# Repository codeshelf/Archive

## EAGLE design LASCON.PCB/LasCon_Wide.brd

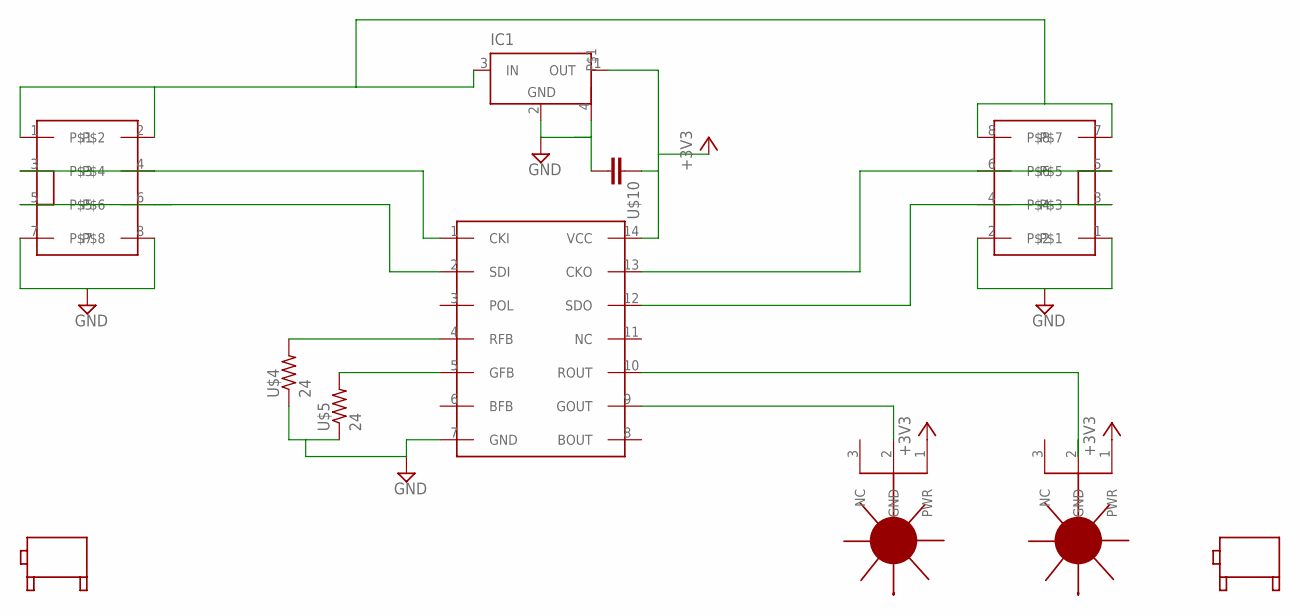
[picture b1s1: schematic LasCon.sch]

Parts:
IC1: MCP1804T-3302I; SOT223
U$1, U$2: 2X4IDC; 2X04
U$3: WS2801; SO14
U$4, U$5: 24; RF-C0805
U$6, U$7: LASER
U$8, U$9: 90DEGMNT
U$10: RF-C0805; C0805

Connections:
+3V3: IC1.1 (OUT), U$3.14 (VCC), U$6.1 (PWR), U$7.1 (PWR), U$10.1
GND: IC1.2 (GND), IC1.4, U$1.7, U$1.8, U$2.1, U$2.2, U$3.7 (GND), U$4.1, U$5.1, U$10.2
unnamed: IC1.3 (IN), U$1.1, U$1.2, U$2.7, U$2.8
unnamed: U$3.9 (GOUT), U$6.2 (GND)
unnamed: U$3.10 (ROUT), U$7.2 (GND)
unnamed: U$1.3, U$1.4, U$3.1 (CKI)
unnamed: U$1.5, U$1.6, U$3.2 (SDI)
unnamed: U$2.5, U$2.6, U$3.13 (CKO)
unnamed: U$2.3, U$2.4, U$3.12 (SDO)
unnamed: U$3.4 (RFB), U$4.2
unnamed: U$3.5 (GFB), U$5.2

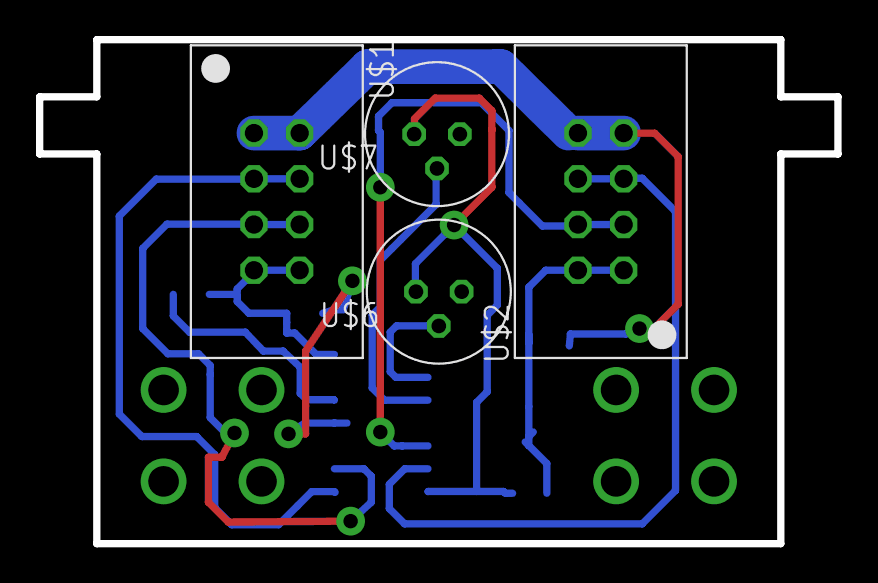
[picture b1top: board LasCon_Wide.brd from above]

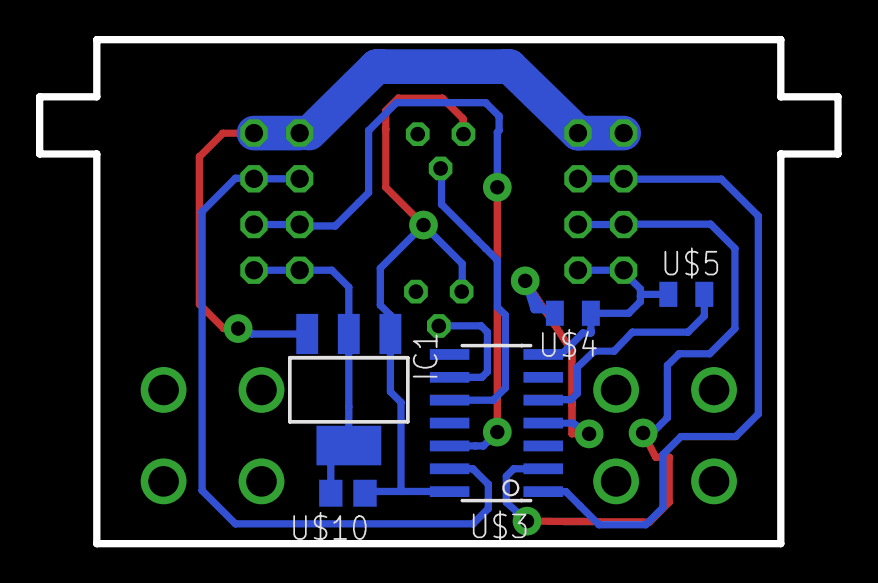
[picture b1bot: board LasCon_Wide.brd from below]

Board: 2 copper layers, 44.4 x 28.0 mm, 11 parts (5 on the bottom side), 11 nets.

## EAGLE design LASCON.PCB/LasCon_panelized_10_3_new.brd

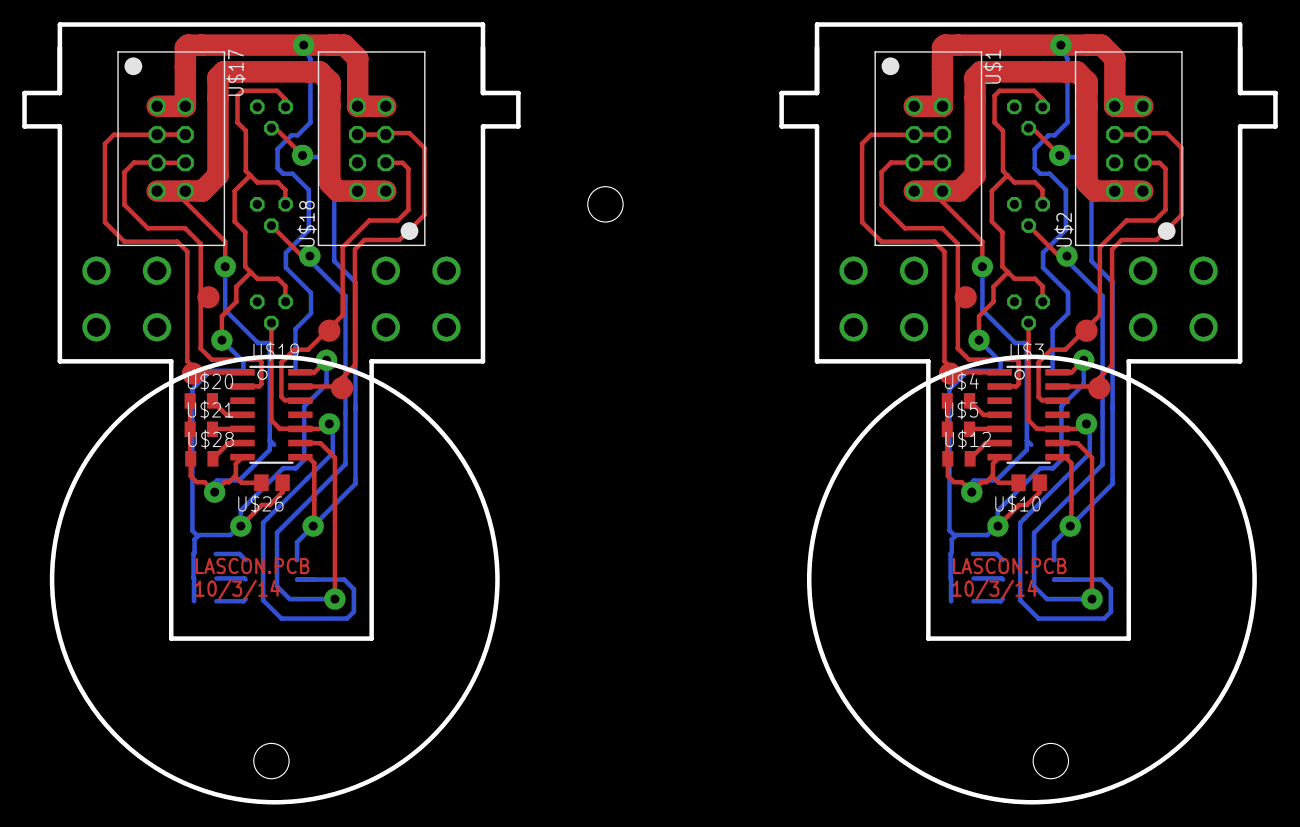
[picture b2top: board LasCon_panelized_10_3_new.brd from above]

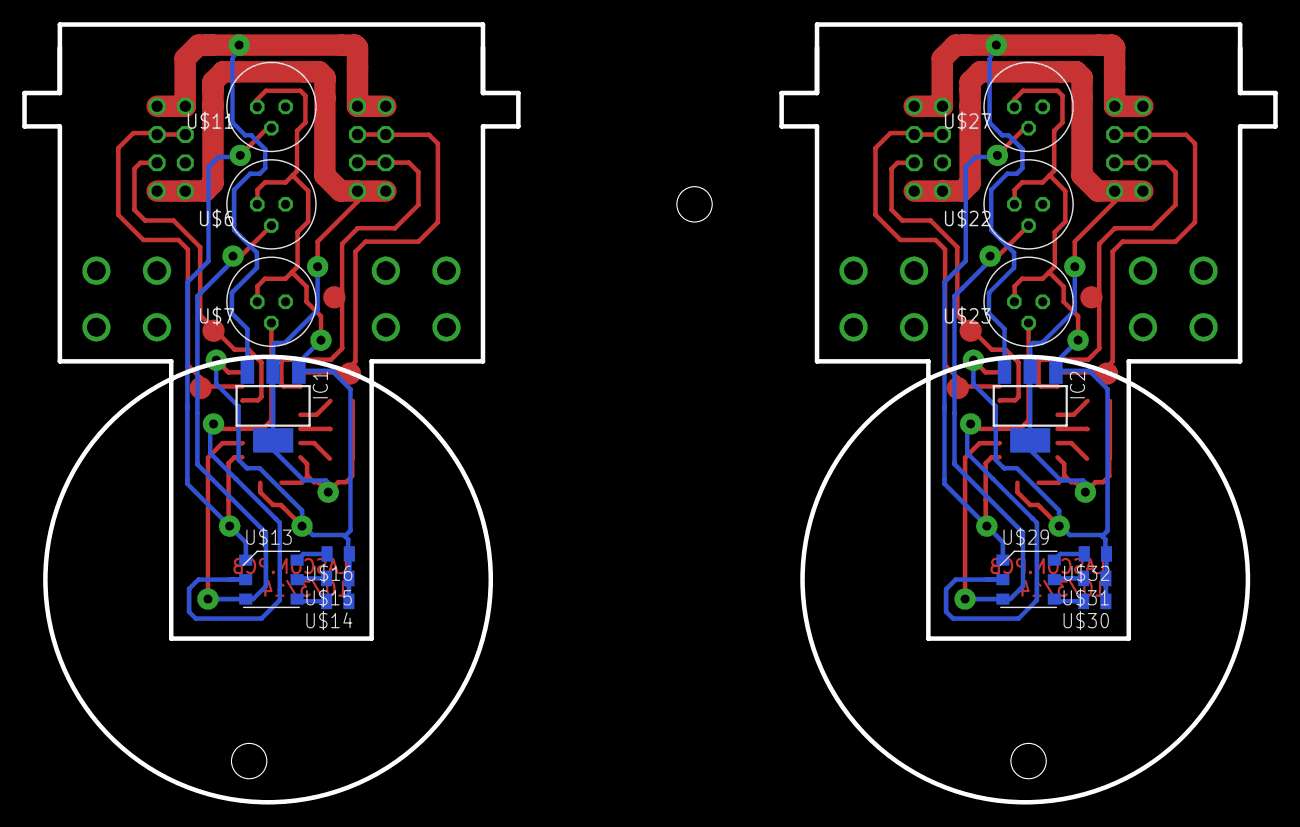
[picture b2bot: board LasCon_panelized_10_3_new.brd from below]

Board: 2 copper layers, 112.3 x 69.8 mm, 34 parts (16 on the bottom side), 32 nets.

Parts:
IC1, IC2: SOT223
U$1, U$2, U$17, U$18: 2X4IDC; 2X04
U$3, U$19: WS2801; SO14
U$4, U$5, U$12, U$14, U$15, U$16, U$20, U$21, U$28, U$30, U$31, U$32: 24; RF-C0805
U$6, U$7, U$11, U$22, U$23, U$27: LASER
U$8, U$9, U$24, U$25: 90DEGMNT
U$10, U$26: C0805
U$13, U$29: LED5060A; PLCC-6

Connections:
+3V1: IC2.1, U$19.14, U$22.1, U$23.1, U$26.1, U$27.1, U$30.1, U$31.1, U$32.1
+3V3: IC1.1, U$3.14, U$6.1, U$7.1, U$10.1, U$11.1, U$14.1, U$15.1, U$16.1
GND: IC1.2, IC1.4, U$1.7, U$1.8, U$2.1, U$2.2, U$3.7, U$4.1, U$5.1, U$10.2, U$12.1
GND1: IC2.2, IC2.4, U$17.7, U$17.8, U$18.1, U$18.2, U$19.7, U$20.1, U$21.1, U$26.2, U$28.1
unnamed: IC1.3, U$1.1, U$1.2, U$2.7, U$2.8
unnamed: U$3.9, U$6.2, U$13.3
unnamed: U$3.10, U$7.2, U$13.2
unnamed: U$3.8, U$11.2, U$13.1
unnamed: U$1.3, U$1.4, U$3.1
unnamed: U$1.5, U$1.6, U$3.2
unnamed: U$2.5, U$2.6, U$3.13
unnamed: U$2.3, U$2.4, U$3.12
unnamed: U$3.4, U$4.2
unnamed: U$3.5, U$5.2
unnamed: U$3.6, U$12.2
unnamed: U$13.4, U$14.2
unnamed: U$13.5, U$15.2
unnamed: U$13.6, U$16.2
unnamed: IC2.3, U$17.1, U$17.2, U$18.7, U$18.8
unnamed: U$17.3, U$17.4, U$19.1
unnamed: U$17.5, U$17.6, U$19.2
unnamed: U$18.5, U$18.6, U$19.13
unnamed: U$18.3, U$18.4, U$19.12
unnamed: U$19.4, U$20.2
unnamed: U$19.5, U$21.2
unnamed: U$19.10, U$23.2, U$29.2
unnamed: U$19.9, U$22.2, U$29.3
unnamed: U$19.8, U$27.2, U$29.1
unnamed: U$19.6, U$28.2
unnamed: U$29.4, U$30.2
unnamed: U$29.5, U$31.2
unnamed: U$29.6, U$32.2

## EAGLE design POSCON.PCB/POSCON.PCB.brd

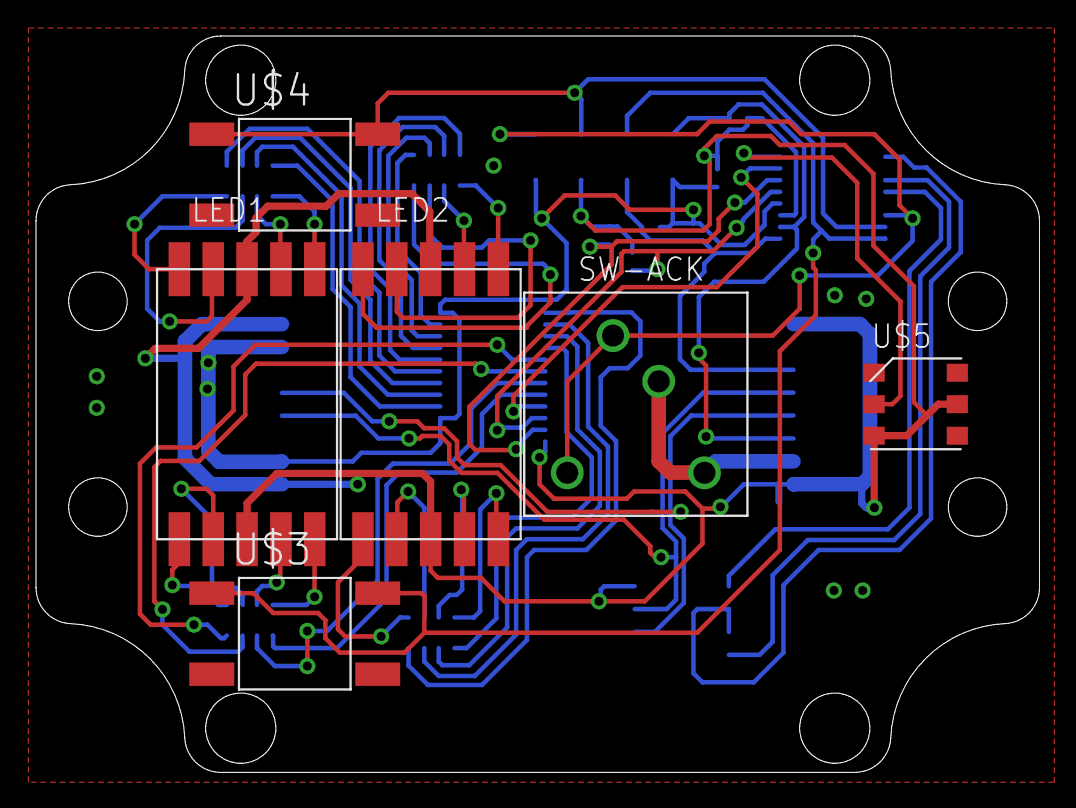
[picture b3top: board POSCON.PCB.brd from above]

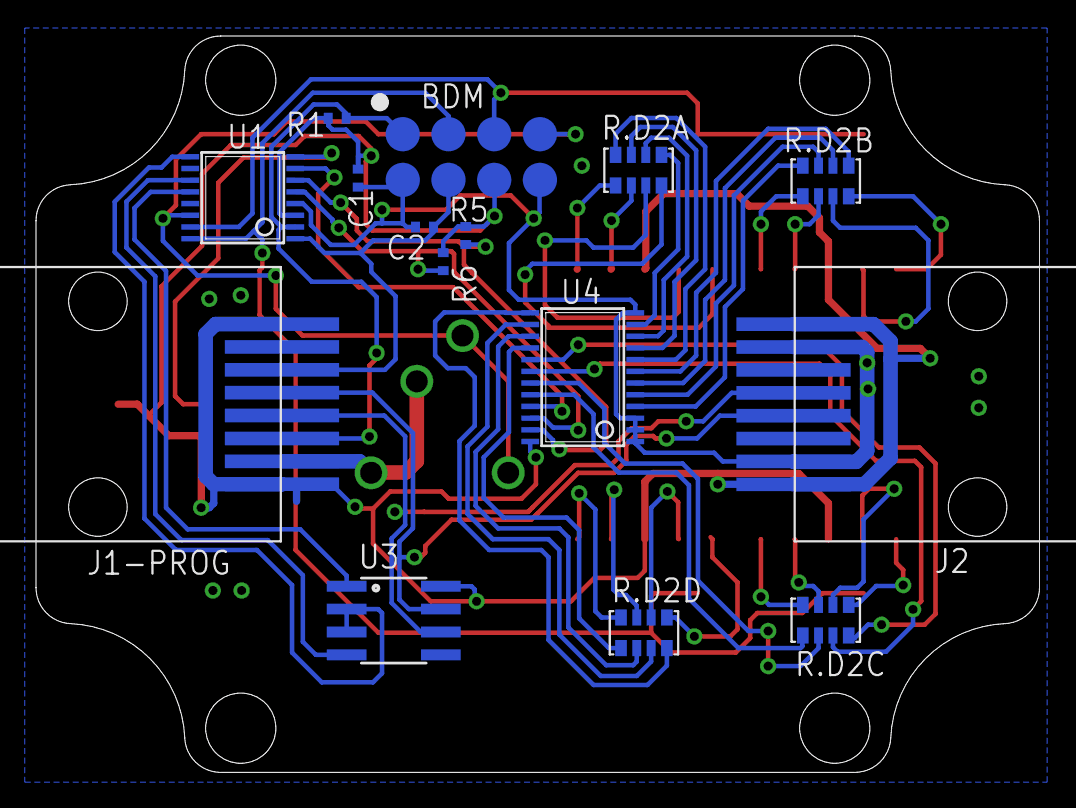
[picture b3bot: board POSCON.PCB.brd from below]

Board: 2 copper layers, 55.8 x 40.9 mm, 21 parts (15 on the bottom side), 48 nets.

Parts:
BDM: TP2X4SMD; SMD4X2
C1, C2: .1uF; C0402
J1-PROG, J2: RJ45-8; MOLEX-0955016649
LED1, LED2: 7SEGMENT-1DIGITSMD; 7SEGMENT-1DIG-.40-SMD
R1: 3.3K; RF-R0402
R5, R6: 10K; RF-R0402
R.D2A, R.D2B, R.D2C, R.D2D: RESISTOR-ARRAY-4X-3216; 3216-4X
SW-ACK: SWITCH-TACTILE-320.01E11WHT
U1: MC9S08QG-DT; TSSOP16
U3: RS485SOIC; SO08
U4: PCA9552; TSSOP24
U$3, U$4: SWITCH-TACTILE; ESWITCH-TL3301PF
U$5: WS2812; PLCC-6

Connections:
485_N: J1-PROG.P$4, J2.P$4, U3.7
485_P: J1-PROG.P$5, J2.P$5, U3.6
+3V3: BDM.P$6, C1.1, J1-PROG.P$1, J1-PROG.P$8, J2.P$1, J2.P$8, LED1.3, LED1.8, LED2.3, LED2.8, R1.2, R5.2, R6.2, U1.3, U3.8, U4.24, U$5.3, U$5.5
GND: BDM.P$2, BDM.P$8, C1.2, C2.1, J1-PROG.P$2, J1-PROG.P$7, J2.P$2, J2.P$7, SW-ACK.P$3, SW-ACK.P$4, U1.4, U3.5, U4.1, U4.2, U4.3, U4.12, U$3.3, U$3.4, U$4.3, U$4.4, U$5.6
unnamed: R.D2A.5, U4.11
unnamed: U1.8, U$5.2
unnamed: R.D2A.6, U4.10
unnamed: BDM.P$1, J1-PROG.P$6, R1.1, U1.2
unnamed: R.D2A.7, U4.9
unnamed: R.D2A.8, U4.8
unnamed: R.D2B.5, U4.7
unnamed: R.D2B.6, U4.6
unnamed: R.D2B.7, U4.5
unnamed: R.D2B.8, U4.4
unnamed: LED2.6, R.D2A.1
unnamed: LED2.7, R.D2A.2
unnamed: LED2.9, R.D2A.3
unnamed: U1.9, U3.2, U3.3
unnamed: LED2.10, R.D2A.4
unnamed: LED2.5, R.D2D.8
unnamed: LED2.4, R.D2D.7
unnamed: BDM.P$4, C2.2, J1-PROG.P$3, U1.1
unnamed: LED2.2, R.D2D.6
unnamed: LED2.1, R.D2D.5
unnamed: LED1.6, R.D2B.1
unnamed: LED1.7, R.D2B.2
unnamed: LED1.9, R.D2B.3
unnamed: LED1.10, R.D2B.4
unnamed: LED1.5, R.D2C.8
unnamed: R.D2D.4, U4.13
unnamed: R.D2D.3, U4.14
unnamed: R.D2D.2, U4.15
unnamed: R.D2D.1, U4.16
unnamed: R.D2C.4, U4.17
unnamed: R.D2C.3, U4.18
unnamed: R.D2C.2, U4.19
unnamed: R.D2C.1, U4.20
unnamed: LED1.4, R.D2C.7
unnamed: LED1.2, R.D2C.6
unnamed: LED1.1, R.D2C.5
unnamed: BDM.P$7, SW-ACK.P$1, SW-ACK.P$2, U1.14
unnamed: BDM.P$5, U1.15, U$4.1, U$4.2
unnamed: BDM.P$3, U1.16, U$3.1, U$3.2
RESET: U1.7, U4.21
RX: U1.12, U3.1
SLA: R5.1, U1.6, U4.23
SLC: R6.1, U1.5, U4.22
TX: U1.11, U3.4
